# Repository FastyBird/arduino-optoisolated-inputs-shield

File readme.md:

# Optoisolated inputs for Arduino

This is arduino shield schema and borad for optoisolation of arduino's inputs

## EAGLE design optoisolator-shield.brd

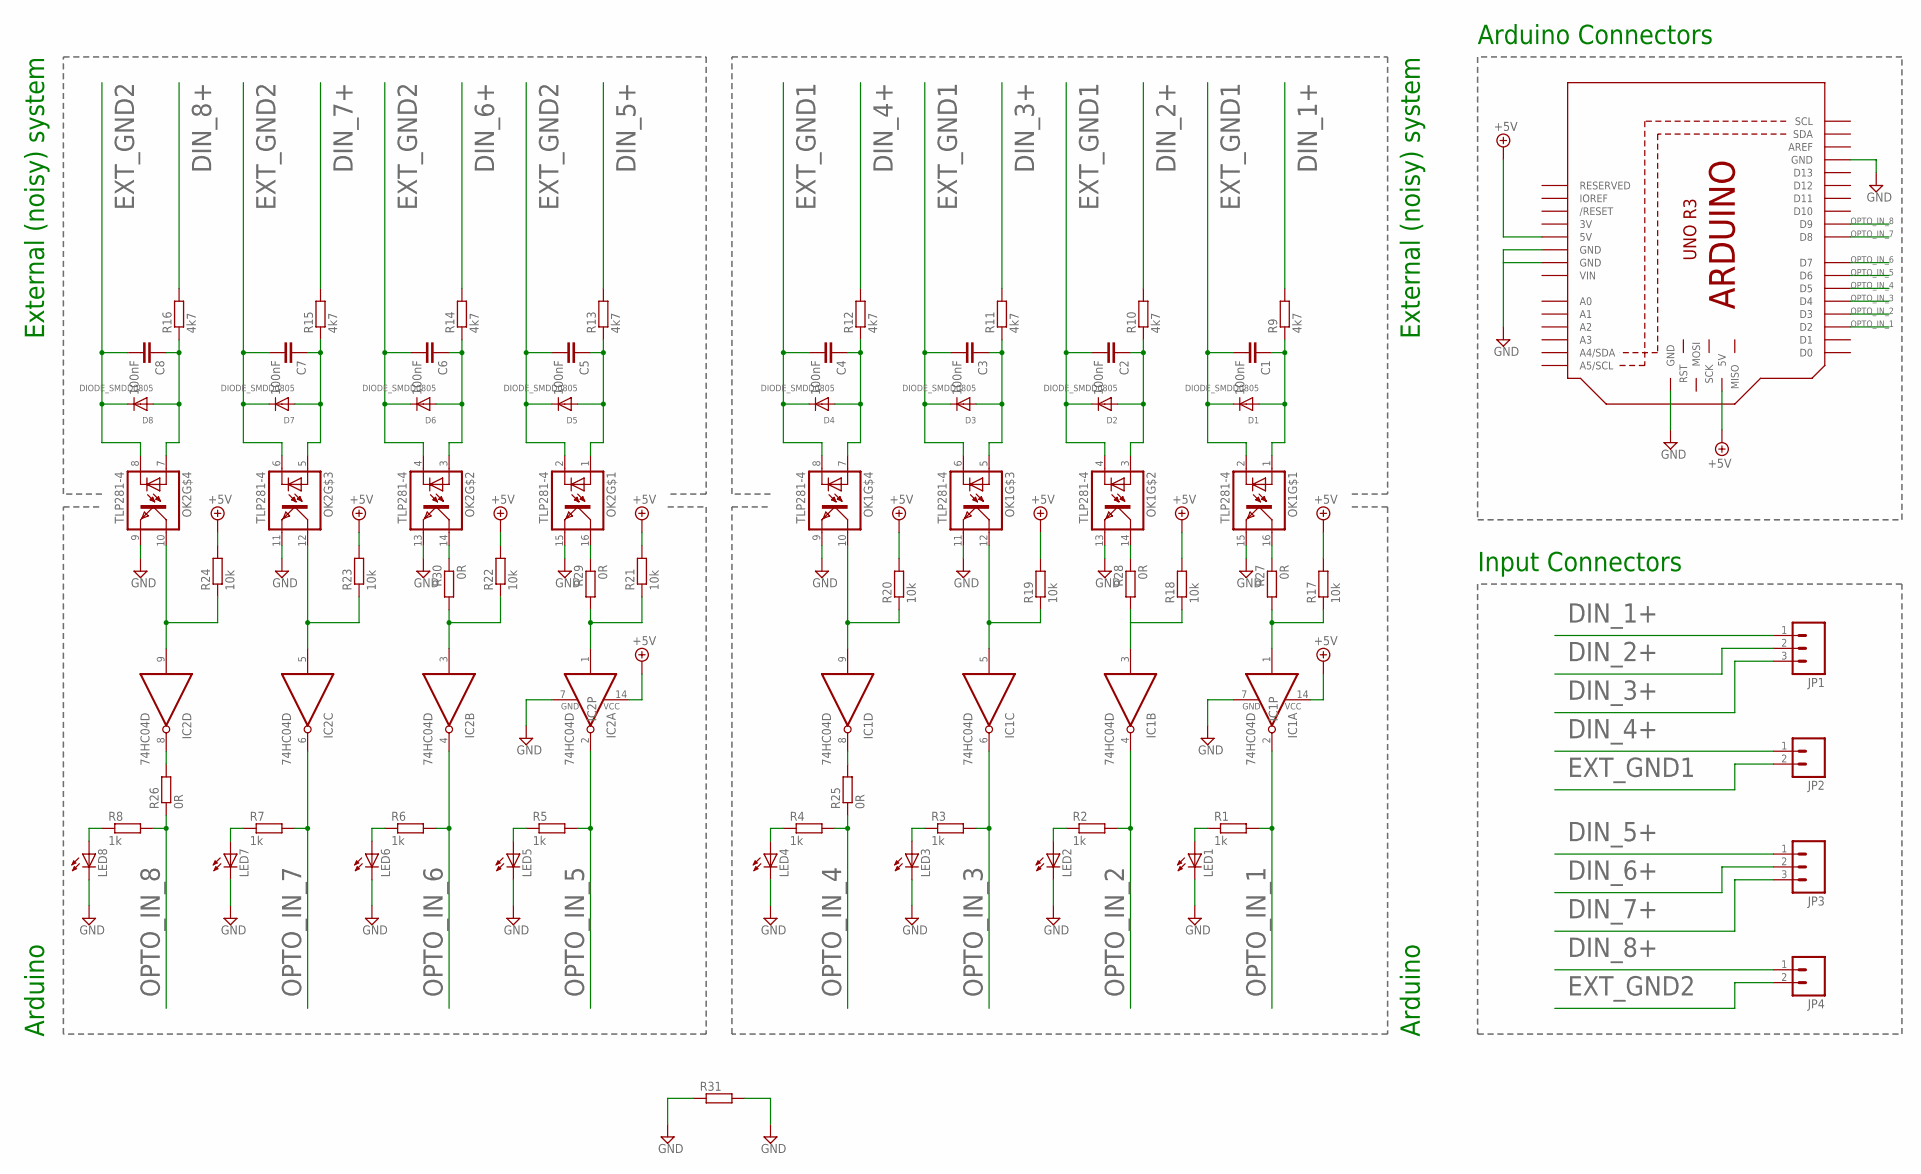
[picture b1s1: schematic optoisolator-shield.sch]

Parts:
C1, C2, C3, C4, C5, C6, C7, C8: 100nF; C0603K
D1, D2, D3, D4, D5, D6, D7, D8: DIODE_SMDD0805; D0805
IC1, IC2: 74HC04D; SO14
JP1, JP3: M03SCREW_LOCK; SCREWTERMINAL-3.5MM-3_LOCK.007S
JP2, JP4: M023.5MM; SCREWTERMINAL-3.5MM-2
LED1, LED2, LED3, LED4, LED5, LED6, LED7, LED8: LEDSML1206; SML1206
M1: ARDUINO_R3_ICSP; ARDUINOR3_ICSP
OK1, OK2: TLP281-4; MINI-FLAT-16
R1, R2, R3, R4, R5, R6, R7, R8: 1k; R0603
R9, R10, R11, R12, R13, R14, R15, R16: 4k7; R0603
R17, R18, R19, R20, R21, R22, R23, R24: 10k; R0603
R25, R26, R27, R28, R29, R30: 0R; R2010
R31: R-EU_R1206; R1206

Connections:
3V: M1.3V
+5V: IC1.14 (VCC), IC2.14 (VCC), M1.5V, M1.5V_ICSP (5V), R17.2, R18.2, R19.2, R20.2, R21.2, R22.2, R23.2, R24.2
DIN_1+: JP1.1, R9.2
DIN_2+: JP1.2, R10.2
DIN_3+: JP1.3, R11.2
DIN_4+: JP2.1, R12.2
DIN_5+: JP3.1, R13.2
DIN_6+: JP3.2, R14.2
DIN_7+: JP3.3, R15.2
DIN_8+: JP4.1, R16.2
EXT_GND1: C1.2, C2.2, C3.2, C4.2, D1.K, D2.K, D3.K, D4.K, JP2.2, OK1.2 (C), OK1.4 (C), OK1.6 (C), OK1.8 (C)
EXT_GND2: C5.2, C6.2, C7.2, C8.2, D5.K, D6.K, D7.K, D8.K, JP4.2, OK2.2 (C), OK2.4 (C), OK2.6 (C), OK2.8 (C)
GND: IC1.7 (GND), IC2.7 (GND), LED1.C, LED2.C, LED3.C, LED4.C, LED5.C, LED6.C, LED7.C, LED8.C, M1.GND, M1.GND@1 (GND), M1.GND@2 (GND), M1.GND@3 (GND), OK1.9 (EMIT), OK1.11 (EMIT), OK1.13 (EMIT), OK1.15 (EMIT), OK2.9 (EMIT), OK2.11 (EMIT), OK2.13 (EMIT), OK2.15 (EMIT), R31.1, R31.2
unnamed: IC1.1 (I), R17.1, R27.2
unnamed: IC1.3 (I), R18.1, R28.2
unnamed: IC1.5 (I), OK1.12 (COL), R19.1
unnamed: IC1.9 (I), OK1.10 (COL), R20.1
unnamed: IC2.1 (I), R21.1, R29.2
unnamed: IC2.3 (I), R22.1, R30.2
unnamed: IC2.5 (I), OK2.12 (COL), R23.1
unnamed: IC2.9 (I), OK2.10 (COL), R24.1
unnamed: OK2.16 (COL), R29.1
unnamed: IC1.8 (O), R25.2
unnamed: IC2.8 (O), R26.2
unnamed: OK1.16 (COL), R27.1
unnamed: OK1.14 (COL), R28.1
unnamed: OK2.14 (COL), R30.1
unnamed: C1.1, D1.A, OK1.1 (A), R9.1
unnamed: C2.1, D2.A, OK1.3 (A), R10.1
unnamed: C3.1, D3.A, OK1.5 (A), R11.1
unnamed: C4.1, D4.A, OK1.7 (A), R12.1
unnamed: C5.1, D5.A, OK2.1 (A), R13.1
unnamed: C6.1, D6.A, OK2.3 (A), R14.1
unnamed: C7.1, D7.A, OK2.5 (A), R15.1
unnamed: C8.1, D8.A, OK2.7 (A), R16.1
unnamed: LED1.A, R1.1
unnamed: LED2.A, R2.1
unnamed: LED3.A, R3.1
unnamed: LED4.A, R4.1
unnamed: LED5.A, R5.1
unnamed: LED6.A, R6.1
unnamed: LED7.A, R7.1
unnamed: LED8.A, R8.1
OPTO_IN_1: IC1.2 (O), M1.D2, R1.2
OPTO_IN_2: IC1.4 (O), M1.D3, R2.2
OPTO_IN_3: IC1.6 (O), M1.D4, R3.2
OPTO_IN_4: M1.D5, R4.2, R25.1
OPTO_IN_5: IC2.2 (O), M1.D6, R5.2
OPTO_IN_6: IC2.4 (O), M1.D7, R6.2
OPTO_IN_7: IC2.6 (O), M1.D8, R7.2
OPTO_IN_8: M1.D9, R8.2, R26.1
VIN: M1.VIN

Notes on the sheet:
Input Connectors
Arduino
External (noisy) system
Arduino Connectors

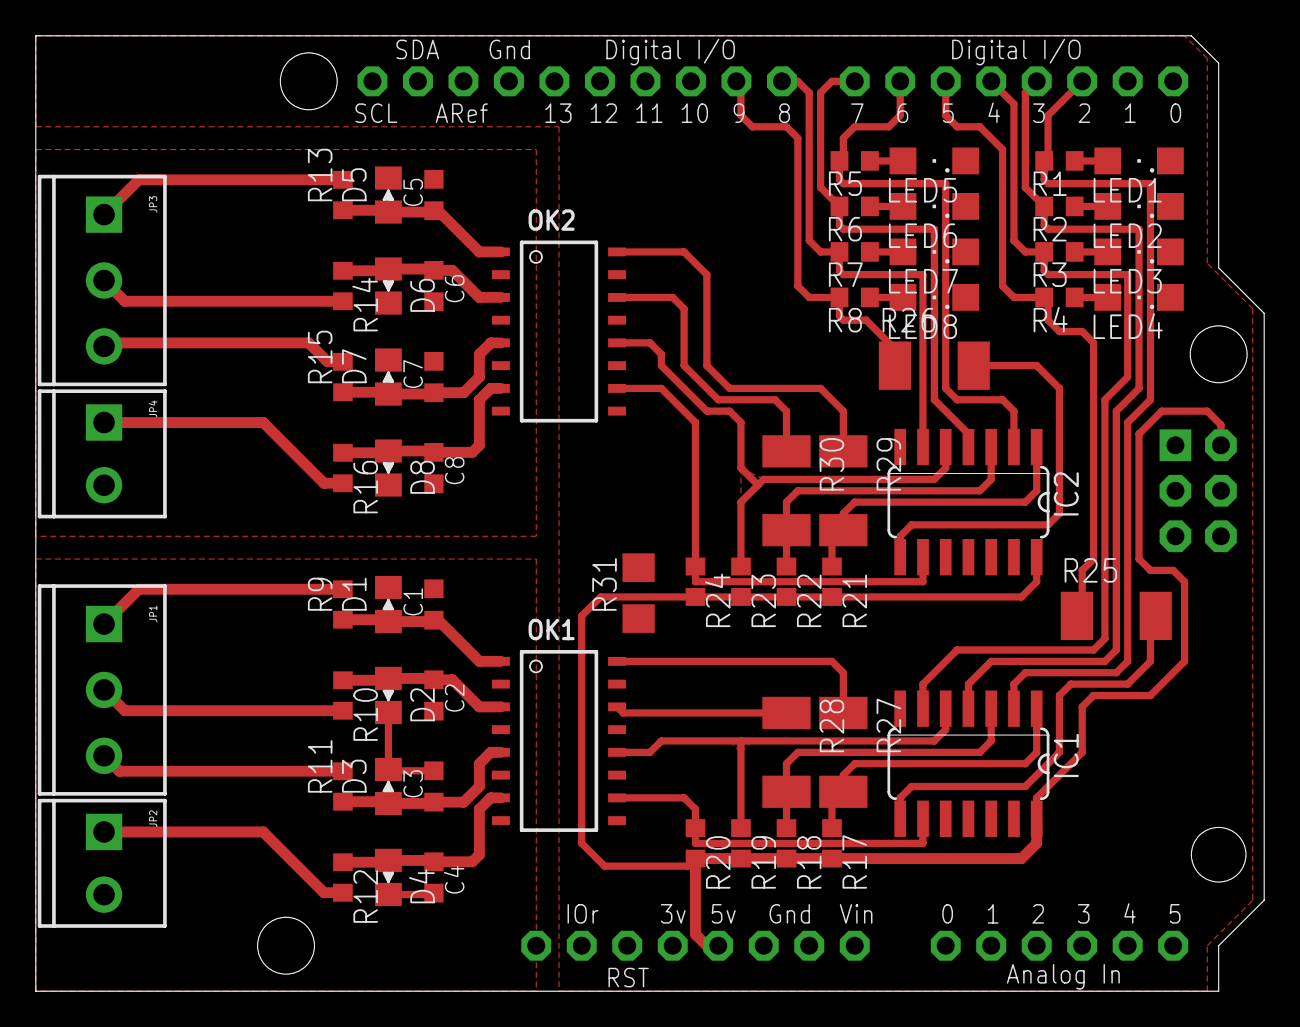
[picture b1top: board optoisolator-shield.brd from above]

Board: 2 copper layers, 68.6 x 53.3 mm, 64 parts (0 on the bottom side), 50 nets.

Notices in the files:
parts and their libraries:
SparkFunOld: Licensing: CC v3.0 Share-Alike You are welcome to use this library for commercial purposes.
